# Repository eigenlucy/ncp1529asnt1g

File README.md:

# ncp1529asnt1g (prelease, untested)

2.7V-5.5Vin -> 900mV-3.9Vout 1.7MHz 1A Buck Converter

Vout set with assertions, just change the value of OUTPUT_VOLTAGE

## Regulator Module

```
Vfb = 600mV

    INPUT_VOLTAGE: voltage
    VIN_MIN = 2.7V
    VIN_MAX = 5.5V
    assert INPUT_VOLTAGE < VIN_MAX; assert INPUT_VOLTAGE > VIN_MIN

    OUTPUT_VOLTAGE: voltage
    VOUT_MIN = 900mV
    VOUT_MAX = 3.9V
    assert OUTPUT_VOLTAGE < VOUT_MAX; assert OUTPUT_VOLTAGE > VOUT_MIN

    Rtop.resistance = ((OUTPUT_VOLTAGE / Vfb) - 1) * Rbottom.resistance
```

## Usage

```
import ElectricPower
from "eigenlucy/ncp1529asnt1g/main.ato" import Regulator

module App:
    power_batt = new ElectricPower # Connect to battery
    power_3V3 = new ElectricPower # 3V3 rail, supplied by regulator

    ldo = new Regulator
    ldo.OUTPUT_VOLTAGE = 3.3V +/- 5%
    ldo.Vin ~ power_batt
    ldo.Vout ~ power_3V3
    # ldo.ic.EN ~ uc.gpioX # Connect EN pin (active high)
```

## TODO

- Solve input cap and output LC filter with assertions
- Solve for Iq and test if within limits

Created by lucy moglia <eigenlucy@proton.me>

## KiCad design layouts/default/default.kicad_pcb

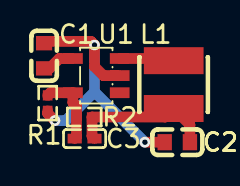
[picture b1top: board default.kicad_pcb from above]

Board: 2 copper layers, 7 parts (0 on the bottom side), 5 nets.

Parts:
C1, C2: 100nF ±10% 50V X7R; C0603-bd72f6
C3: 100nF ±10% 16V X7R; C0402-b3ef17
L1: IND-SMD_L3.0-W3.0-a13401
R1: 200kΩ ±1% 62.5mW; R0402-56259e
R2: 100kΩ ±1% 62.5mW; R0402-56259e
U1: SOT-23-5_L3.0-W1.7-P0.95-LS2.8-BR-9d80aa

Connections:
FB: C3.2, R1.1, R2.2, U1.5
SW: L1.1, U1.3
VIN: C1.1, U1.4
gnd: C1.2, C2.2, R1.2, U1.2
hv: C2.1, C3.1, L1.2, R2.1

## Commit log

2025-04-29 added assertions and layout
2025-04-29 ready for release
2025-04-29 fixed oops
2025-04-29 readme
2025-04-29 changed app to regulator
2025-05-26 removed default voltage, changed readme
2025-05-26 added enable pin note
